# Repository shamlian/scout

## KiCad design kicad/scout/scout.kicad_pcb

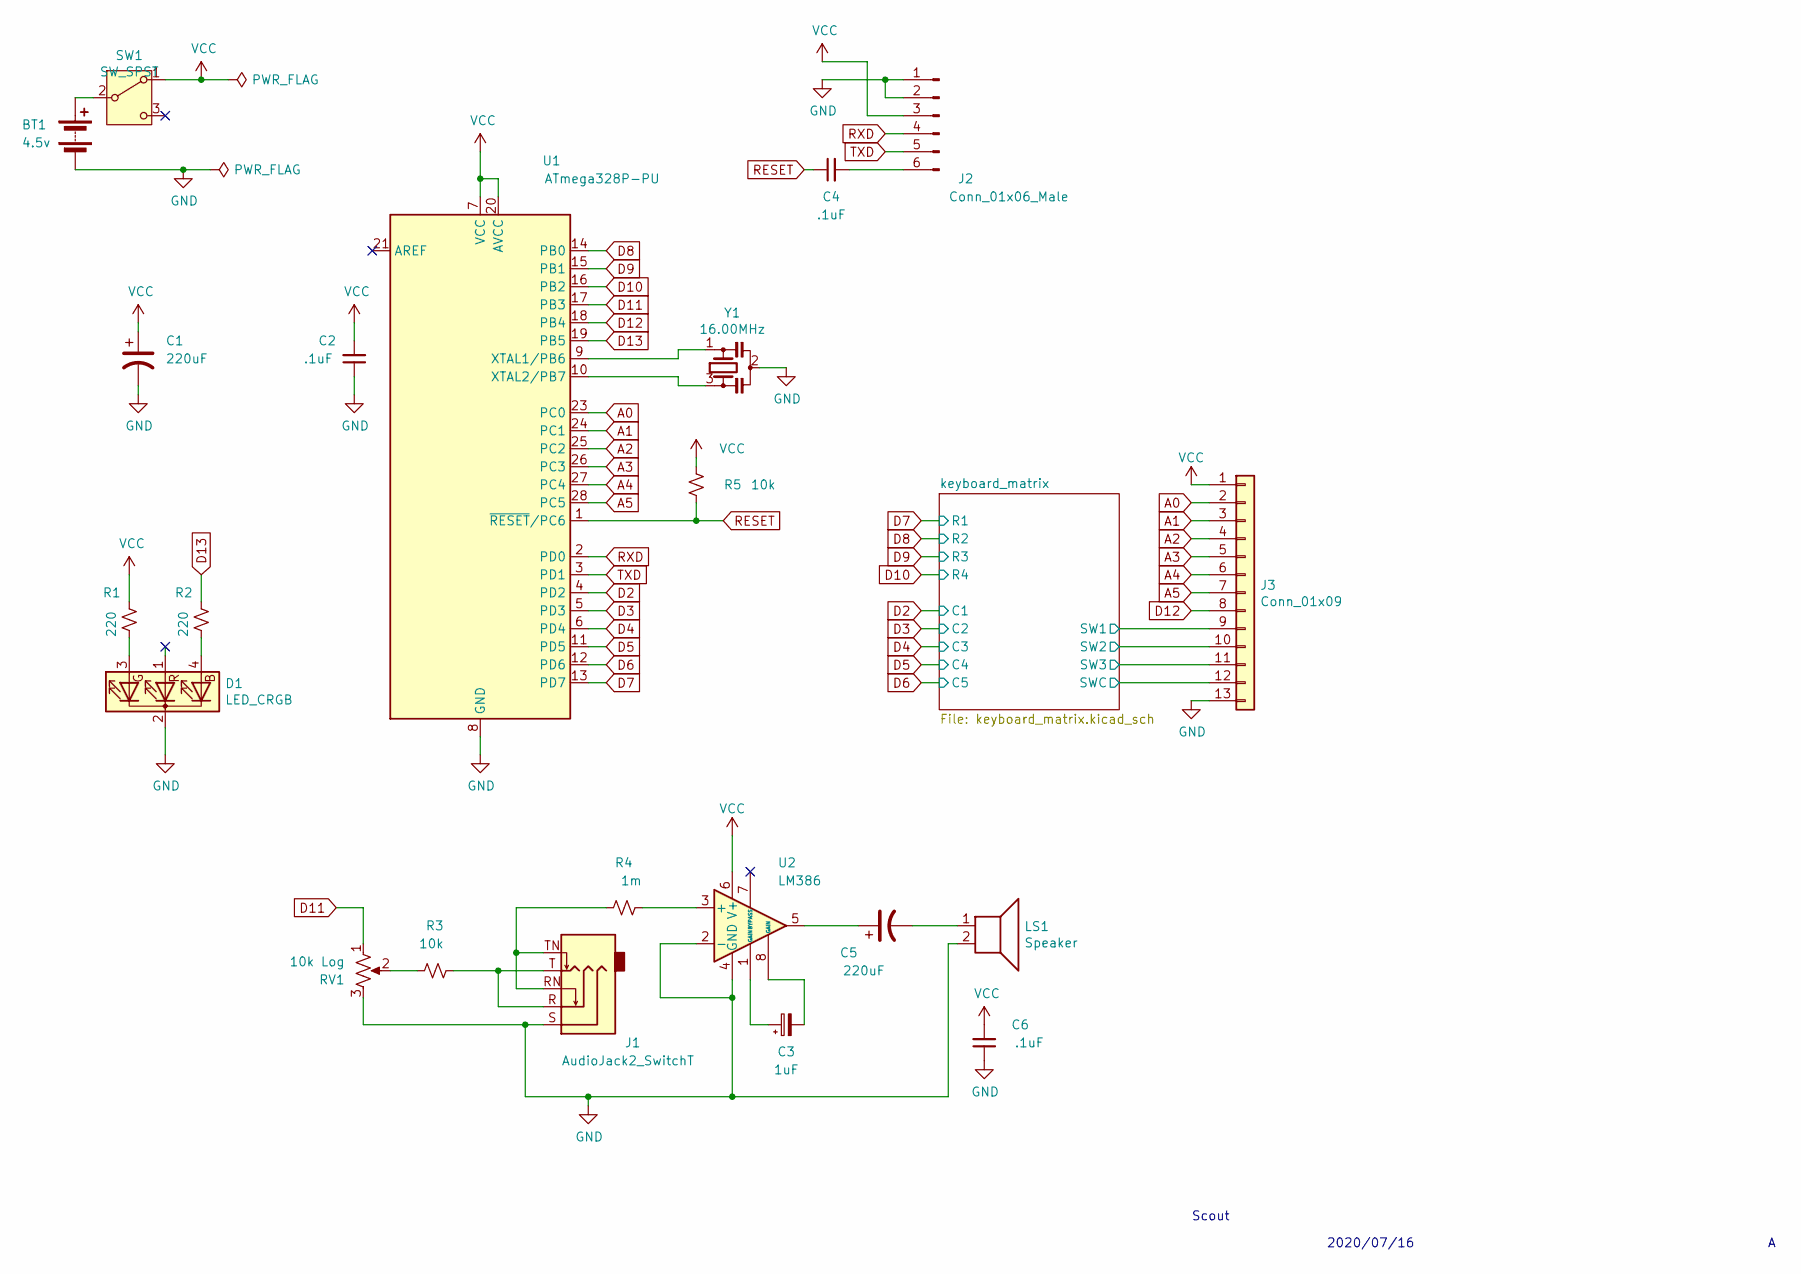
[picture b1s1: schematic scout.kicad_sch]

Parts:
BT1: 4.5v; PinHeader_1x02_P2.54mm_Vertical
C1, C5: 220uF; CP_Radial_D8.0mm_P3.50mm
C2, C4, C6: .1uF; C_Disc_D5.0mm_W2.5mm_P5.00mm
C3: 1uF; CP_Radial_D5.0mm_P2.00mm
D1: LED_CRGB; LED_D5.0mm-4_RGB_Staggered_Pins
J1: AudioJack2_SwitchT; AUDIO-JACK
J2: Conn_01x06_Male; PinHeader_1x06_P2.54mm_Horizontal
J3: Conn_01x09; PinHeader_1x13_P2.54mm_Vertical
LS1: Speaker; PinHeader_1x02_P2.54mm_Vertical
R1, R2: 220; R_Axial_DIN0207_L6.3mm_D2.5mm_P10.16mm_Horizontal
R3, R5: 10k; R_Axial_DIN0207_L6.3mm_D2.5mm_P10.16mm_Horizontal
R4: 1m; R_Axial_DIN0207_L6.3mm_D2.5mm_P10.16mm_Horizontal
RV1: 10k Log; Potentiometer_Bourns_PTV09A-1_Single_Vertical
SW1: SW_SPST; SW_Slide_1P2T_CK_OS102011MS2Q
U1: ATmega328P-PU; DIP-28_W7.62mm
U2: LM386; DIP-8_W7.62mm
Y1: 16.00MHz; Resonator-3Pin_W7.0mm_H2.5mm

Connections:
/keyboard_matrix/SW1: J3.9; also elsewhere on the board
/keyboard_matrix/SW2: J3.10; also elsewhere on the board
/keyboard_matrix/SW3: J3.11; also elsewhere on the board
A0: J3.2, U1.23 (PC0)
A1: J3.3, U1.24 (PC1)
A2: J3.4, U1.25 (PC2)
A3: J3.5, U1.26 (PC3)
A4: J3.6, U1.27 (PC4)
A5: J3.7, U1.28 (PC5)
D2: U1.4 (PD2); also elsewhere on the board
D3: U1.5 (PD3); also elsewhere on the board
D4: U1.6 (PD4); also elsewhere on the board
D5: U1.11 (PD5); also elsewhere on the board
D6: U1.12 (PD6); also elsewhere on the board
D7: U1.13 (PD7); also elsewhere on the board
D8: U1.14 (PB0); also elsewhere on the board
D9: U1.15 (PB1); also elsewhere on the board
D10: J3.12, U1.16 (PB2); also elsewhere on the board
D11: RV1.1, U1.17 (PB3)
D12: J3.8, U1.18 (PB4)
D13: R2.1, U1.19 (PB5)
GND: BT1.2 (-), C1.2, C2.1, C6.1, D1.2 (K), J1.S, J2.1, J2.2, J3.13, LS1.2, RV1.3, U1.8 (GND), U1.22 (GND), U2.2 (-), U2.4 (GND), Y1.2
unnamed: BT1.1 (+), SW1.2 (B)
unnamed: C3.1, U2.1 (GAIN)
unnamed: C3.2, U2.8 (GAIN)
unnamed: C5.1, U2.5
unnamed: C5.2, LS1.1
unnamed: D1.4 (BA), R2.2
unnamed: D1.3 (RA), R1.2
unnamed: J1.R, J1.T, R3.2
unnamed: J1.RN, J1.TN, R4.1
unnamed: C4.2, J2.6
unnamed: R3.1, RV1.2
unnamed: U1.9 (XTAL1/PB6), Y1.1
unnamed: U1.10 (XTAL2/PB7), Y1.3
unnamed: R4.2, U2.3 (+)
RESET: C4.1, R5.2, U1.1 (~RESET/PC6)
RXD: J2.4, U1.2 (PD0)
TXD: J2.5, U1.3 (PD1)
VCC: C1.1, C2.2, C6.2, J2.3, J3.1, R1.1, R5.1, SW1.1 (A), U1.7 (VCC), U1.20 (AVCC), U2.6 (V+)

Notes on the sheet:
Scout
2020/07/16

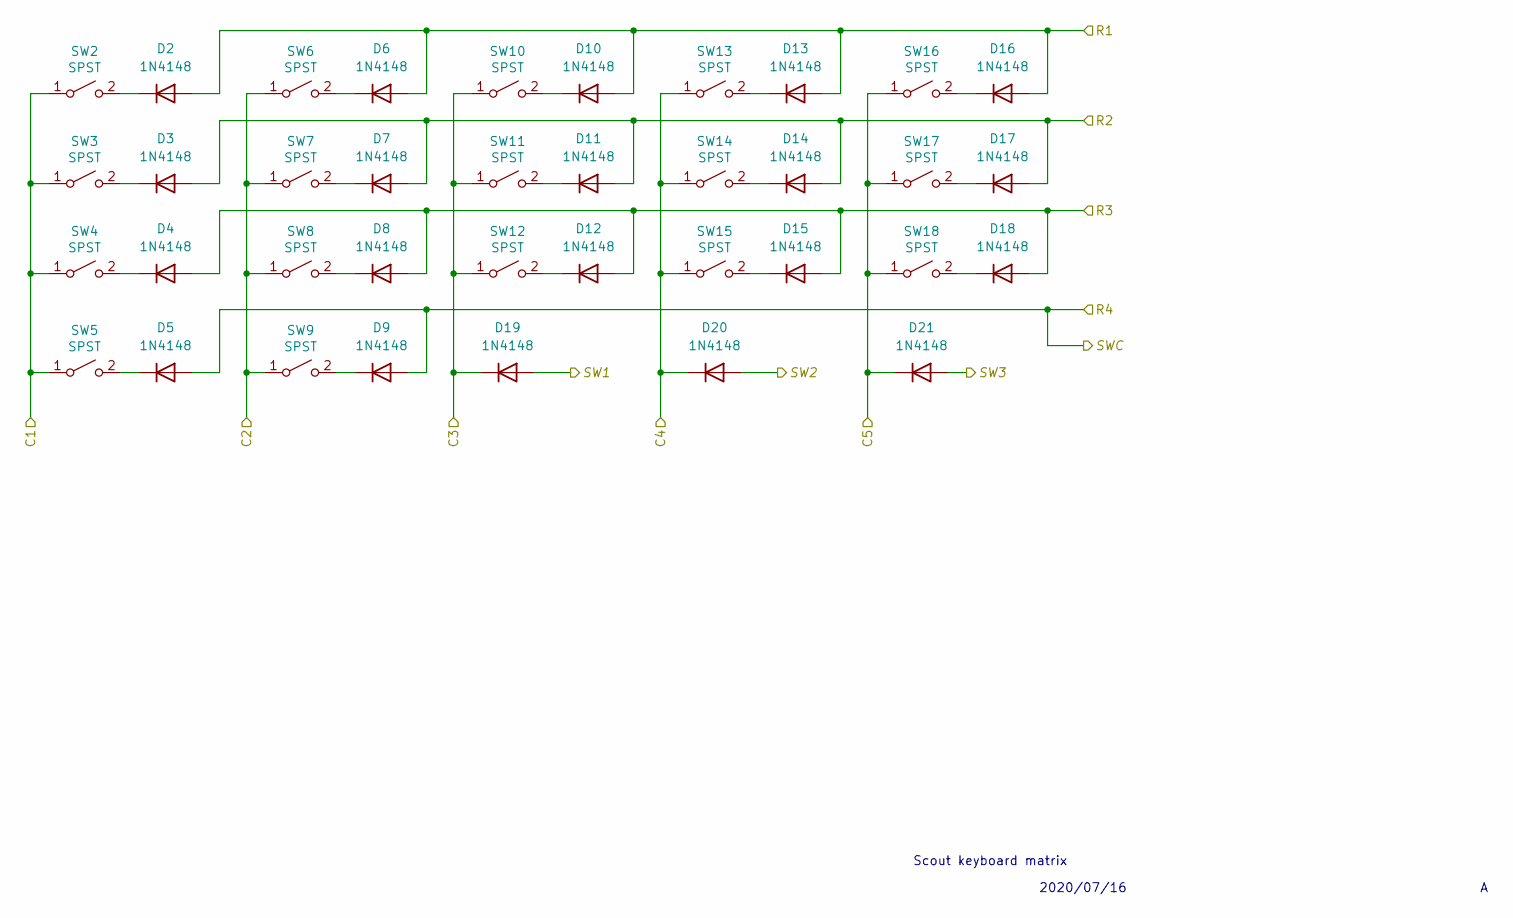
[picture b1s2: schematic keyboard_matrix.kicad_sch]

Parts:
D2, D3, D4, D5, D6, D7, D8, D9, D10, D11, D12, D13, D14, D15, D16, D17, D18, D19, D20, D21: 1N4148; D_DO-35_SOD27_P7.62mm_Horizontal
SW2, SW3, SW4, SW5, SW6, SW7, SW8, SW9, SW10, SW11, SW12, SW13, SW14, SW15, SW16, SW17, SW18: SPST; SW_PUSH_6mm

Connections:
/keyboard_matrix/SW1: D19.2 (A); also elsewhere on the board
/keyboard_matrix/SW2: D20.2 (A); also elsewhere on the board
/keyboard_matrix/SW3: D21.2 (A); also elsewhere on the board
D2: SW2.1 (A), SW3.1 (A), SW4.1 (A), SW5.1 (A); also elsewhere on the board
D3: SW6.1 (A), SW7.1 (A), SW8.1 (A), SW9.1 (A); also elsewhere on the board
D4: D19.1 (K), SW10.1 (A), SW11.1 (A), SW12.1 (A); also elsewhere on the board
D5: D20.1 (K), SW13.1 (A), SW14.1 (A), SW15.1 (A); also elsewhere on the board
D6: D21.1 (K), SW16.1 (A), SW17.1 (A), SW18.1 (A); also elsewhere on the board
D7: D2.2 (A), D6.2 (A), D10.2 (A), D13.2 (A), D16.2 (A); also elsewhere on the board
D8: D3.2 (A), D7.2 (A), D11.2 (A), D14.2 (A), D17.2 (A); also elsewhere on the board
D9: D4.2 (A), D8.2 (A), D12.2 (A), D15.2 (A), D18.2 (A); also elsewhere on the board
D10: D5.2 (A), D9.2 (A); also elsewhere on the board
unnamed: D2.1 (K), SW2.2 (B)
unnamed: D3.1 (K), SW3.2 (B)
unnamed: D4.1 (K), SW4.2 (B)
unnamed: D5.1 (K), SW5.2 (B)
unnamed: D6.1 (K), SW6.2 (B)
unnamed: D7.1 (K), SW7.2 (B)
unnamed: D8.1 (K), SW8.2 (B)
unnamed: D9.1 (K), SW9.2 (B)
unnamed: D10.1 (K), SW10.2 (B)
unnamed: D11.1 (K), SW11.2 (B)
unnamed: D12.1 (K), SW12.2 (B)
unnamed: D13.1 (K), SW13.2 (B)
unnamed: D14.1 (K), SW14.2 (B)
unnamed: D15.1 (K), SW15.2 (B)
unnamed: D16.1 (K), SW16.2 (B)
unnamed: D17.1 (K), SW17.2 (B)
unnamed: D18.1 (K), SW18.2 (B)

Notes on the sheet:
2020/07/16
Scout keyboard matrix

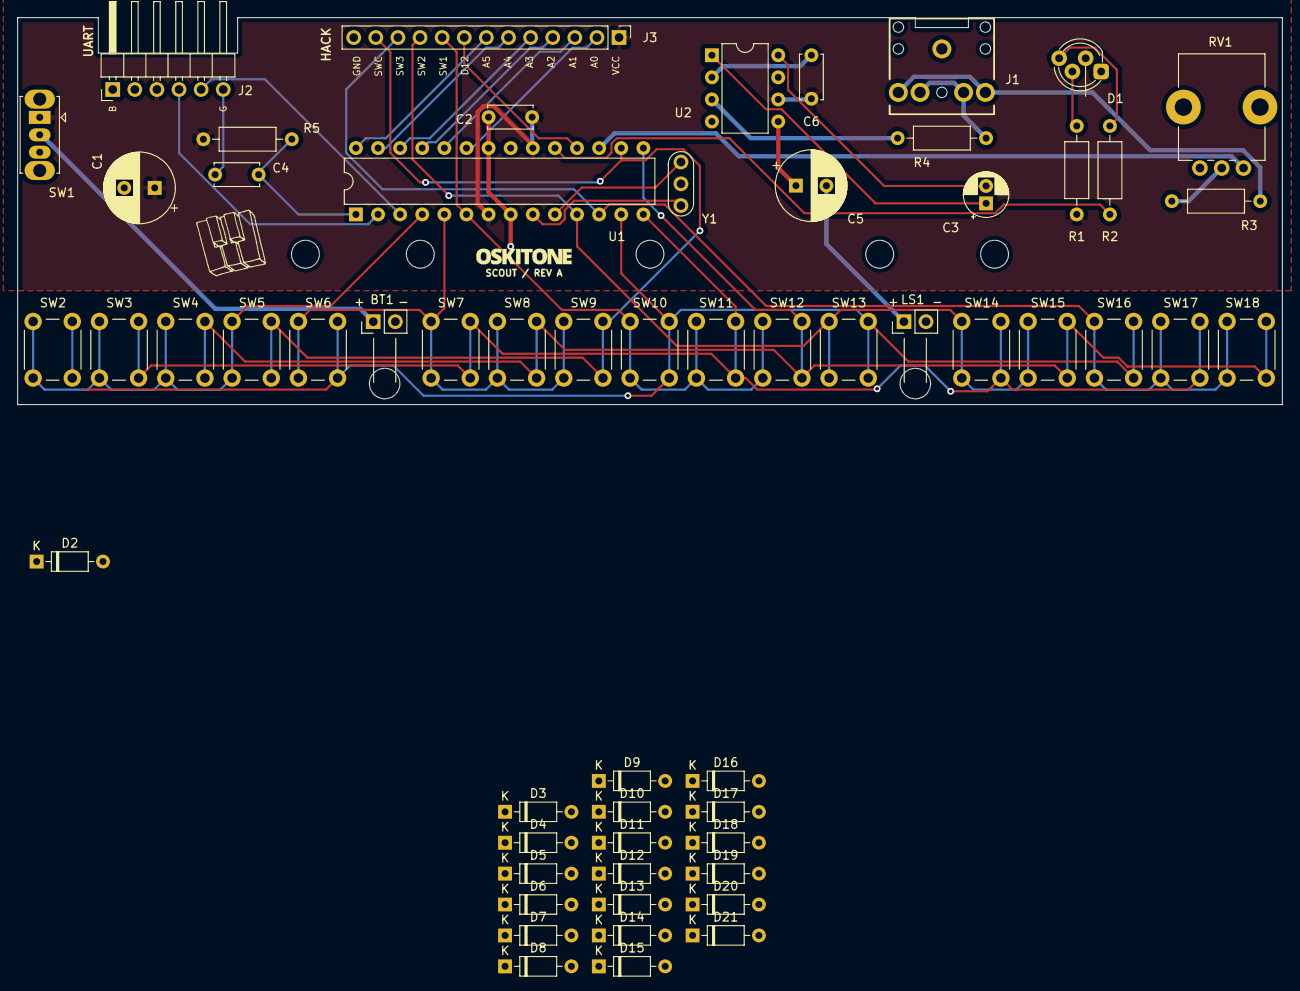
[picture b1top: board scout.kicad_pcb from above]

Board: 2 copper layers, 145.3 x 44.5 mm, 68 parts (0 on the bottom side), 57 nets.

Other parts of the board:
 : MountingHole_3.5mm
 #2: MountingHole_3.5mm
 #3,  #4,  #5,  #6,  #7: MountingHole_3.2mm_M3
Ref**: Val**; logo
Ref**#2: Val**; branding

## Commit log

2021-09-13 Arpeggios and no glide
    Hacked out the slick Frequency object and made a mess of the KeyBuffer abstraction to bring arpeggios to Scout.
2021-09-13 Strip remainder of Frequency
    Committing to my laziness by getting rid of anything related to Frequency (probably, I should do better)
2021-09-13 const int and not #define
    This is C++, you clod.
2025-02-16 Pin swaps for Mozzi
2025-02-16 Add diodes

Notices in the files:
kicad/scout/scout.kicad_pcb:
Designed by Oskitone. CC BY-SA 4.0.
